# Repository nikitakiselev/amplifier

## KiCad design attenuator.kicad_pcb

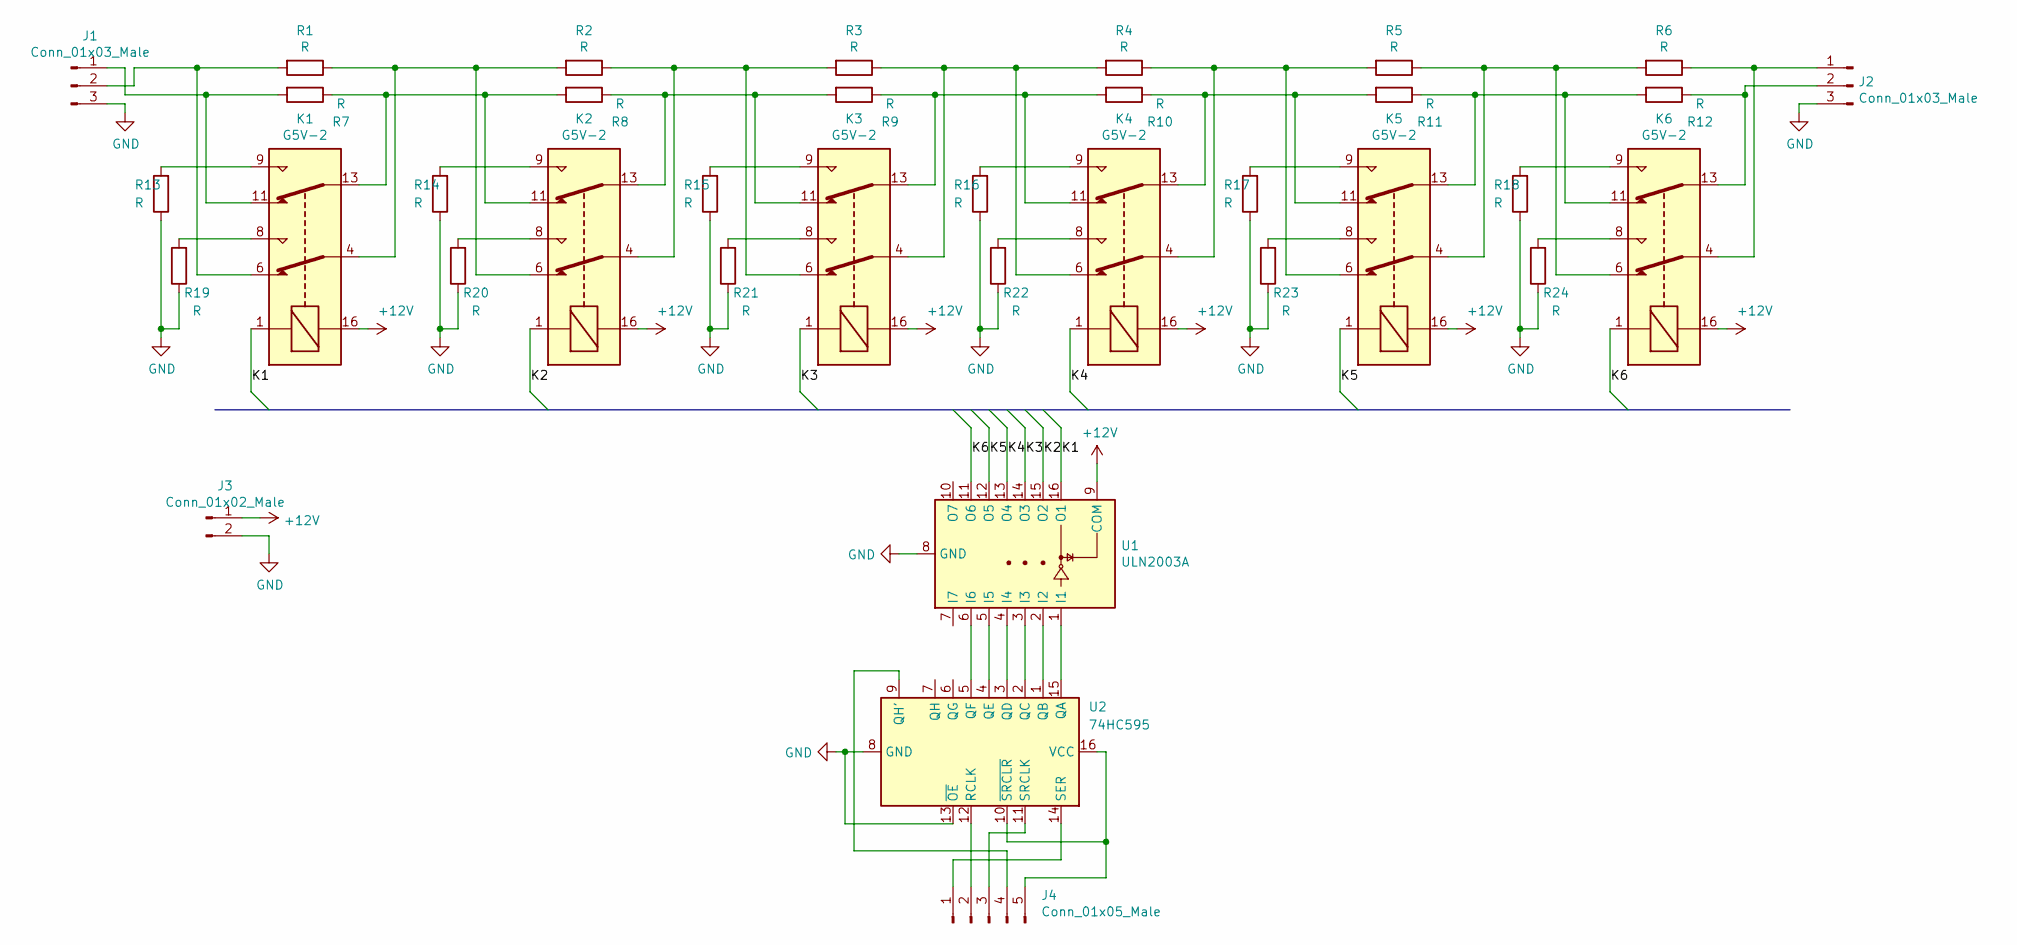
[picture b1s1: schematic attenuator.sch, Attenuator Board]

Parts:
J1, J2: Conn_01x03_Male; Molex_KK-254_AE-6410-03A_1x03_P2.54mm_Vertical
J3: Conn_01x02_Male; Molex_KK-254_AE-6410-02A_1x02_P2.54mm_Vertical
J4: Conn_01x05_Male; IDC-Header_2x05_P2.54mm_Horizontal
K1, K2, K3, K4, K5, K6: G5V-2; Relay_DPDT_Omron_G5V-2
R1, R2, R3, R4, R5, R6, R7, R8, R9, R10, R11, R12, R13, R14, R15, R16, R17, R18, R19, R20, R21, R22, R23, R24: R; R_Axial_DIN0309_L9.0mm_D3.2mm_P12.70mm_Horizontal
U1: ULN2003A; DIP-16_W7.62mm
U2: 74HC595; DIP-16_W7.62mm

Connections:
+12V: J3.1, K1.16, K2.16, K3.16, K4.16, K5.16, K6.16, U1.9 (COM)
/K1: K1.1, U1.16 (O1)
/K2: K2.1, U1.15 (O2)
/K3: K3.1, U1.14 (O3)
/K4: K4.1, U1.13 (O4)
/K5: K5.1, U1.12 (O5)
/K6: K6.1, U1.11 (O6)
GND: J1.3, J2.3, J3.2, R13.1, R14.1, R15.1, R16.1, R17.1, R18.1, R19.1, R20.1, R21.1, R22.1, R23.1, R24.1, U1.8 (GND), U2.8 (GND), U2.13 (~OE)
unnamed: J1.1, K1.11, R7.2
unnamed: J1.2, K1.6, R1.2
unnamed: J2.1, K6.4, R6.1
unnamed: J2.2, K6.13, R12.1
unnamed: J4.1, U2.14 (SER)
unnamed: J4.2, U2.12 (RCLK)
unnamed: J4.3, U2.11 (SRCLK)
unnamed: J4.4, U2.9 (QH')
unnamed: J4.5, J4.7, J4.9, U2.10 (~SRCLR), U2.16 (VCC)
unnamed: K1.4, K2.6, R1.1, R2.2
unnamed: K1.8, R19.2
unnamed: K1.9, R13.2
unnamed: K1.13, K2.11, R7.1, R8.2
unnamed: K2.4, K3.6, R2.1, R3.2
unnamed: K2.8, R20.2
unnamed: K2.9, R14.2
unnamed: K2.13, K3.11, R8.1, R9.2
unnamed: K3.4, K4.6, R3.1, R4.2
unnamed: K3.8, R21.2
unnamed: K3.9, R15.2
unnamed: K3.13, K4.11, R9.1, R10.2
unnamed: K4.4, K5.6, R4.1, R5.2
unnamed: K4.8, R22.2
unnamed: K4.9, R16.2
unnamed: K4.13, K5.11, R10.1, R11.2
unnamed: K5.4, K6.6, R5.1, R6.2
unnamed: K5.8, R23.2
unnamed: K5.9, R17.2
unnamed: K5.13, K6.11, R11.1, R12.2
unnamed: K6.8, R24.2
unnamed: K6.9, R18.2
unnamed: U1.1 (I1), U2.15 (QA)
unnamed: U1.2 (I2), U2.1 (QB)
unnamed: U1.3 (I3), U2.2 (QC)
unnamed: U1.4 (I4), U2.3 (QD)
unnamed: U1.5 (I5), U2.4 (QE)
unnamed: U1.6 (I6), U2.5 (QF)

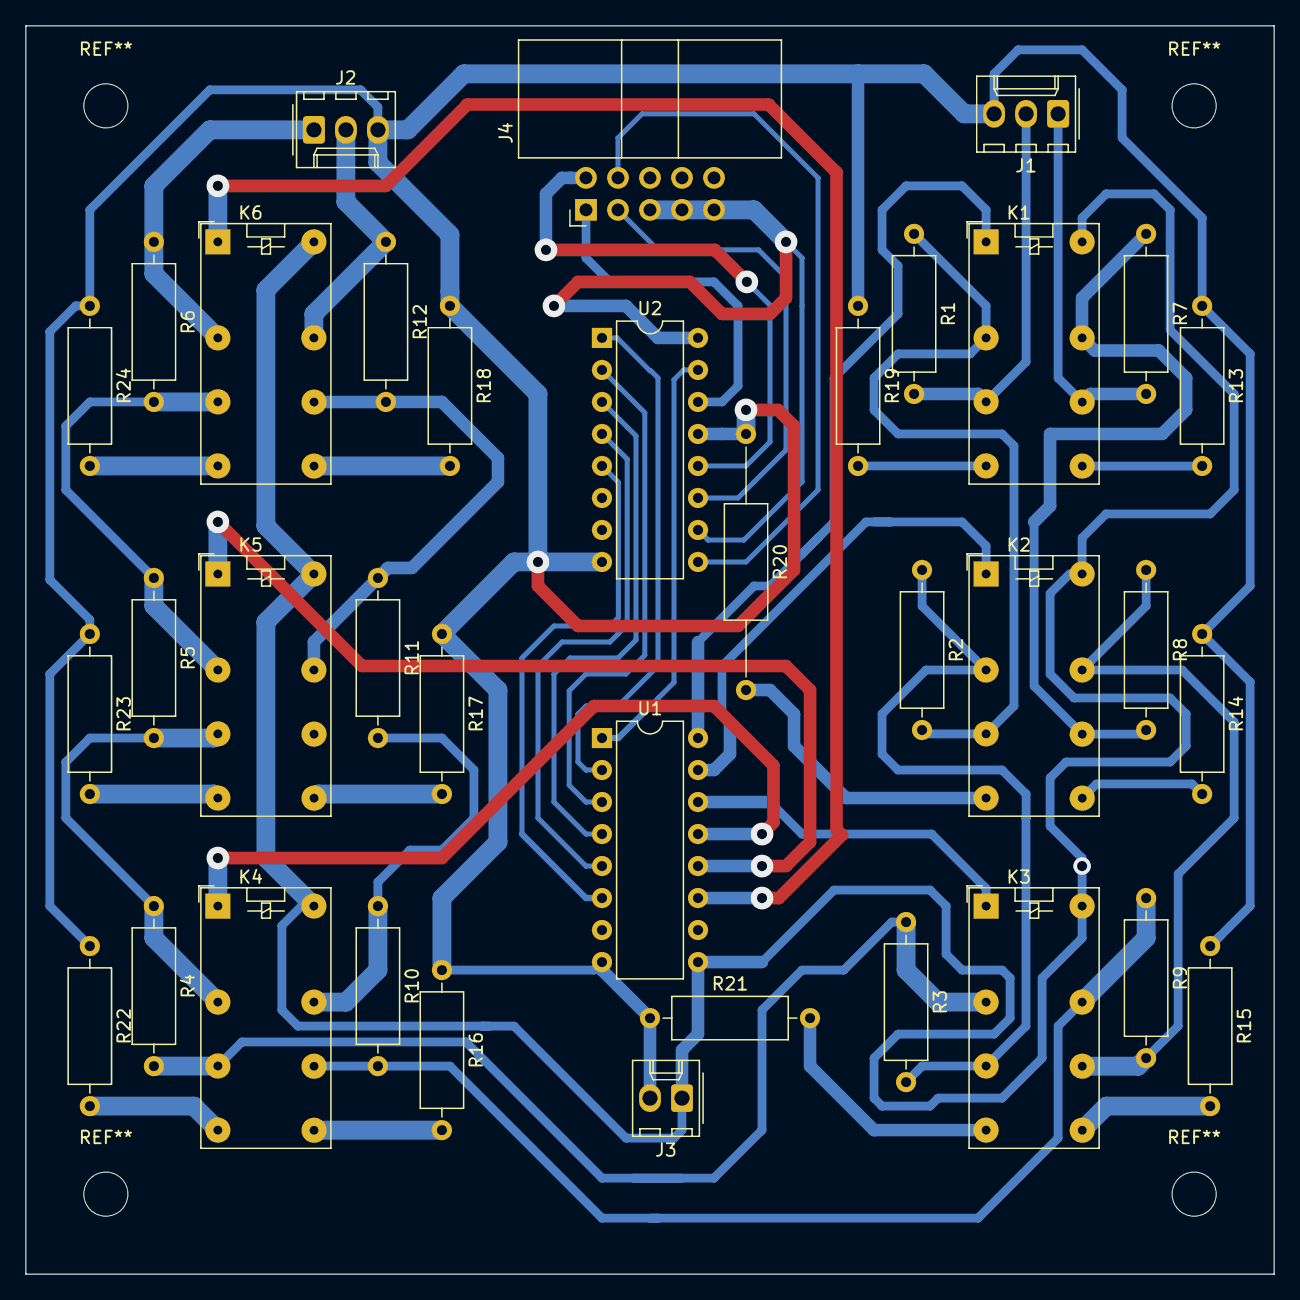
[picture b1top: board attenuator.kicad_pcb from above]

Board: 2 copper layers, 99.1 x 99.1 mm, 36 parts (0 on the bottom side), 45 nets.

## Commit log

2018-11-30 Add attenuator project
2018-11-30 change schema and working on pcb
2018-12-08 Update pcb board
2018-12-08 First version of pcb booard
2018-12-09 Update pcb
